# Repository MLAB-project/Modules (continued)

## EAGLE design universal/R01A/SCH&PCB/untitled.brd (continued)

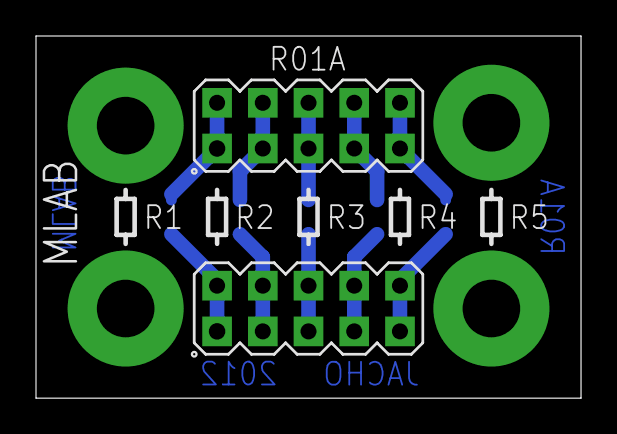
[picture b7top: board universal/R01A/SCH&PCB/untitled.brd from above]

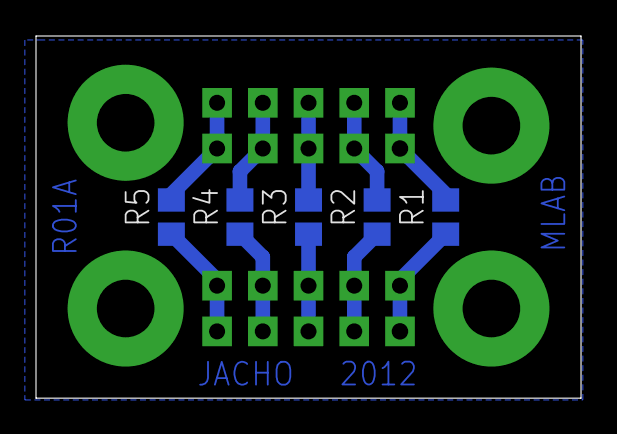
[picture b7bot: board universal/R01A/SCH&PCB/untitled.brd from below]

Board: 2 copper layers, 30.3 x 20.1 mm, 11 parts (5 on the bottom side), 11 nets.

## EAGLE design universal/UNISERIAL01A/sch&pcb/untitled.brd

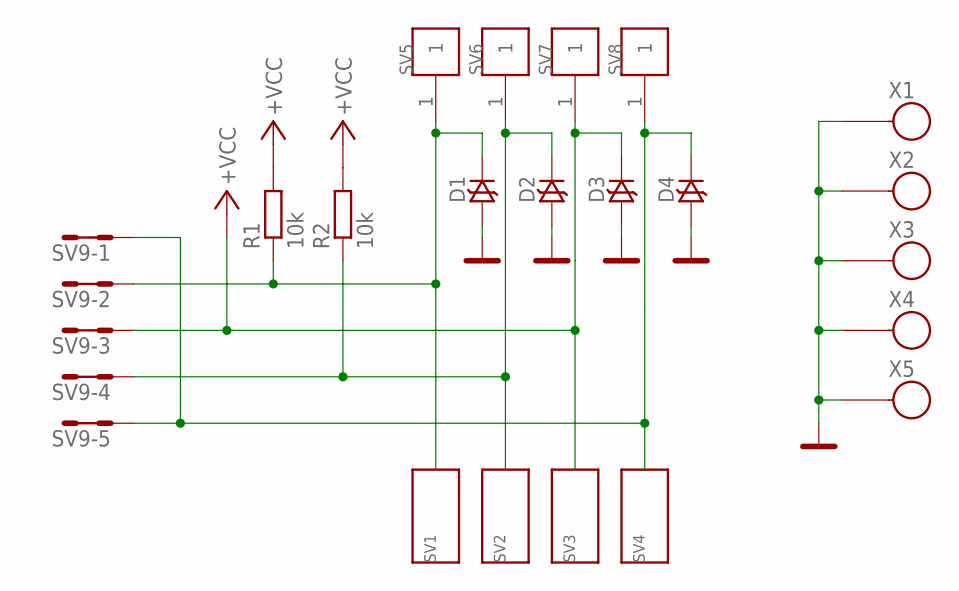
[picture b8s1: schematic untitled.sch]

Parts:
D1, D2, D3, D4: D-TRANSIL-SMA; SMA
R1, R2: 10k; 0805
SV1, SV2, SV3, SV4: WAGO256
SV5, SV6, SV7, SV8: SMD:MA01-01; SMD_MA01-1
SV9: MA05-2
X1, X2, X3, X4, X5: SROUB3M

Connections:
+VCC: D3.K, R1.2, R2.2, SV3.1, SV3.A1, SV7.1, SV9.5, SV9.6
GND: D1.A, D2.A, D3.A, D4.A, X1.P$1, X2.P$1, X3.P$1, X4.P$1, X5.P$1
unnamed: D1.K, R1.1, SV1.1, SV1.A1, SV5.1, SV9.3, SV9.4
unnamed: D2.K, R2.1, SV2.1, SV2.A1, SV6.1, SV9.7, SV9.8
unnamed: D4.K, SV4.1, SV4.A1, SV8.1, SV9.1, SV9.2, SV9.9, SV9.10

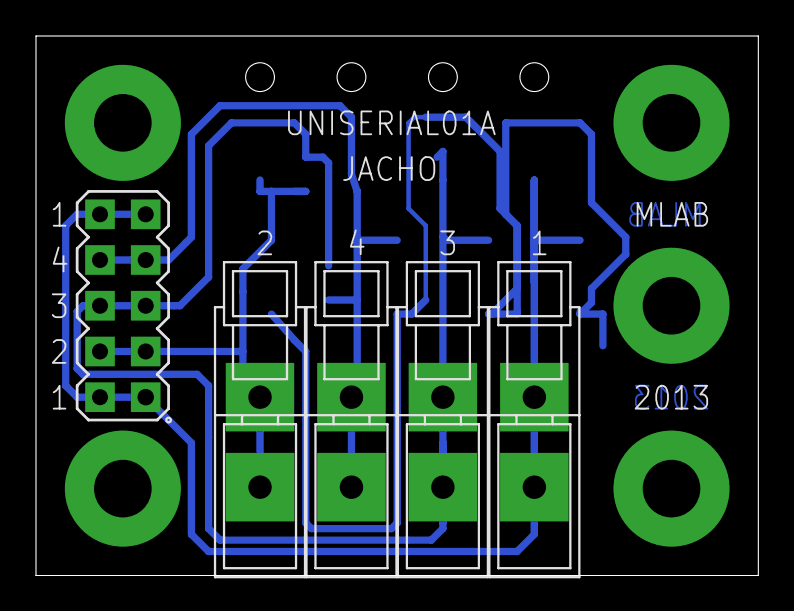
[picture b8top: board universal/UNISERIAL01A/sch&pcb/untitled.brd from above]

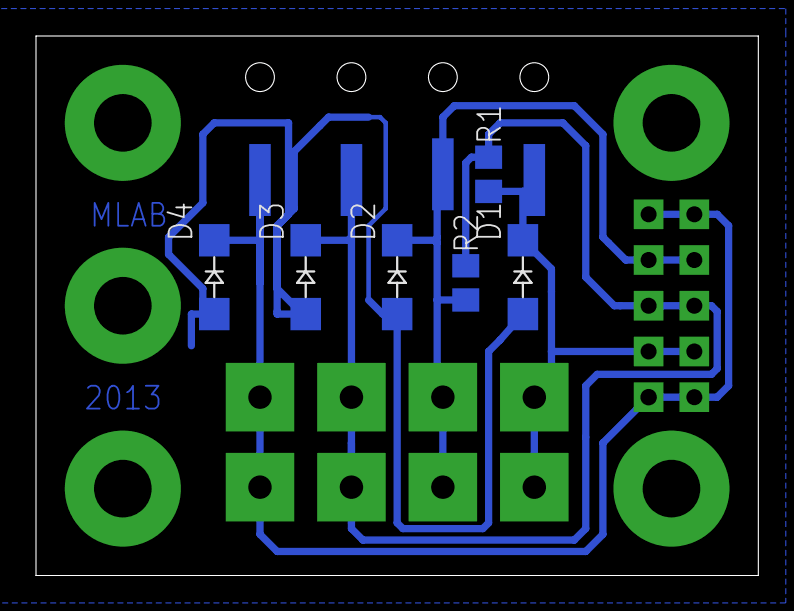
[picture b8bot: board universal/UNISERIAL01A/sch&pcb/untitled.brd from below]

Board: 2 copper layers, 40.1 x 30.0 mm, 20 parts (10 on the bottom side), 5 nets.

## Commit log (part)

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2022-02-16 [MLABweb] Documentation edits; TRIMQUAD01A
2022-02-16 [MLABweb] Documentation edits; LEDbar01A
2022-02-16 [MLABweb] Documentation edits; SDcard01A
2022-02-16 [MLABweb] Documentation edits; PIC16F87xTQ4401A
2022-02-16 [MLABweb] Documentation edits; PICICD01B
2022-02-16 [MLABweb] Documentation edits; Galileo
2022-02-16 [MLABweb] Documentation edits; ATmega8DIL01A
2022-02-16 [MLABweb] Documentation edits; AVRUSB01A
2022-02-16 [MLABweb] Documentation edits; ATmegaTQ10001A
2022-02-16 [MLABweb] Documentation edits; RFM02SMD01A
2022-02-16 [MLABweb] Documentation edits; BP01A
2022-02-16 [MLABweb] Documentation edits; PCRD01A
2022-02-16 [MLABweb] Documentation edits; S3AN01B
2022-02-16 [MLABweb] Documentation edits; LDD01A
2022-02-16 [MLABweb] Documentation edits; SMA2SATA01A
2022-02-16 [MLABweb] Documentation edits; HBRIDGE02A
2022-02-16 [MLABweb] Documentation edits; HBRIDGE01B
2022-02-16 [MLABweb] Documentation edits; MPC17511HB01A
2022-02-16 [MLABweb] Documentation edits; S3AN01A
2022-02-16 [MLABweb] Documentation edits; OZquad01A
2022-02-16 [MLABweb] Documentation edits; POWERDAC01A
2022-02-16 [MLABweb] Documentation edits; MBA81001A
2022-02-16 [MLABweb] Documentation edits; NFET2X01A
2022-02-16 [MLABweb] Documentation edits; PWMLED01A
2022-02-16 [MLABweb] Documentation edits; CLKGEN01A
2022-02-16 [MLABweb] Documentation edits; USB232R01A
2022-02-16 [MLABweb] Documentation edits; I2CHUB01B
2022-02-16 [MLABweb] Documentation edits; ETH01A
2022-02-16 [MLABweb] Documentation edits; SUPERCAP01A
2022-02-16 [MLABweb] Documentation edits; LION2CELL01C
2022-02-16 [MLABweb] Documentation edits; BATPOWER02A
2022-02-16 [MLABweb] Documentation edits; GPS02A
2022-02-17 [MLABweb] Documentation edits; CLKHUB01A
2022-02-17 Module moved to separate repository https://github.com/mlab-modules/ADCoctoSPI01
2022-02-17 Update submodule.
2022-02-18 Remove redundant files to submodules from the repository.
2022-03-08 TTLLVDS01A moved to separate submodule. https://github.com/mlab-modules/TTLLVDS01
2022-04-03 Add links to datasheets.
2022-04-03 Adding submodule STEPUPDC01A
2022-04-05 Adding USBI2C01A as submodule.
2022-04-05 Adding I2CHUB02 as submodule.
2022-08-14 Moving VCAI2C01 to separate repository. https://github.com/mlab-modules/VCAI2C01
2022-08-14 adding submodules of separate repositories.
2023-02-07 Removing ACOMP01A module. Will be designed from ground in the new repository.
2023-04-01 Removing ADC modules splitted to separate repositories.
2023-05-08 Removing ALBASE modules splitted to separate repositories.
2023-05-08 update split script
2023-05-08 Removing ALBASE1609 modules splitted to separate repositories.
2023-05-08 Removing ALBASE1608 modules splitted to separate repositories.
2023-05-08 Removing ALBASE1505 modules splitted to separate repositories.
2023-05-08 Removing ALBASE1241 modules splitted to separate repositories.
2023-05-08 Removing UNIPOWER02A modules splitted to separate repositories.
2023-05-09 Removing BATPOWER04C modules splitted to separate repositories.
2023-05-09 BATPOWER04 to submodule
2023-05-24 update submodule
2023-05-25 update submodle
2023-05-25 Removing CCP2019V01A modules splitted to separate repositories.
2023-05-25 Removing HCS01A modules splitted to separate repositories.
2023-05-25 Removing PIND01A modules splitted to separate repositories.
2023-05-25 Removing RGBC01A modules splitted to separate repositories.
2023-05-25 Removing RPS01A modules splitted to separate repositories.
2023-05-25 Removing SHT31V01A modules splitted to separate repositories.
2023-05-25 Removing THERMOPHILE01A modules splitted to separate repositories.
2023-05-25 Removing TTLPROBE02A modules splitted to separate repositories.
2023-05-25 Removing I2CDIFF01B modules splitted to separate repositories.
2023-05-25 Removing TTLPECL01A modules splitted to separate repositories.
2023-05-25 Removing HUM01A modules splitted to separate repositories.
2023-05-25 Removing IRFEE01A modules splitted to separate repositories.
2023-05-25 Removing ISL03A modules splitted to separate repositories.
2023-05-25 Removing IUC01A modules splitted to separate repositories.
2023-05-25 Removing LIGHTNING01A modules splitted to separate repositories.
2023-05-25 Removing MAG01A modules splitted to separate repositories.
2023-05-25 Removing Pulse_catch01A modules splitted to separate repositories.
2023-06-20 Removing ADCmonoPPI01A modules splitted to separate repositories.
2023-06-20 Removing ADCmonoSPI01B modules splitted to separate repositories.
2023-06-20 Removing ISPLSI1016A modules splitted to separate repositories.
2023-06-20 Removing S3AN01B modules splitted to separate repositories.
2023-06-20 Removing IRDA01A modules splitted to separate repositories.
2023-06-20 Removing TXIR01B modules splitted to separate repositories.
2023-06-20 Removing STM32F30xRx01A modules splitted to separate repositories.
2023-06-20 Removing ATmega801A modules splitted to separate repositories.
2023-06-20 Removing ATmega8DIL01A modules splitted to separate repositories.
2023-06-20 Removing ATmegaTQ3201A modules splitted to separate repositories.
2023-06-20 Removing ATmegaTQ6401A modules splitted to separate repositories.
2023-06-20 Removing ATprogISPUSB02A modules splitted to separate repositories.
2023-06-20 Removing ATtinySO801B modules splitted to separate repositories.
2023-06-20 Removing PICPROGUSB02A modules splitted to separate repositories.
2023-06-20 Removing PIC16F84SO1801A modules splitted to separate repositories.
2023-06-20 Removing PIC16F87xTQ4401B modules splitted to separate repositories.
2023-06-20 Removing PICPGR301A modules splitted to separate repositories.
2023-06-20 Removing PIC16F87xSO2801A modules splitted to separate repositories.
2023-06-20 Removing PIC16F87xDIL2801A modules splitted to separate repositories.
2023-06-20 Removing PIC18F2550v01A modules splitted to separate repositories.
2023-06-20 Removing PIC16F87xTQ4401A modules splitted to separate repositories.
2023-06-20 Removing RFdetect01A modules splitted to separate repositories.
2023-06-20 Removing BLE01A modules splitted to separate repositories.
2023-06-20 Removing RFM02SMD01A modules splitted to separate repositories.
2023-06-20 Removing TXsaw433MHz01A modules splitted to separate repositories.
2023-06-20 Removing GSM01A modules splitted to separate repositories.
2023-06-20 Removing RFM01SMD01A modules splitted to separate repositories.
2023-06-20 Removing BP01A modules splitted to separate repositories.
2023-06-20 Removing RFMIX01A modules splitted to separate repositories.
2023-06-20 Removing FORX01A modules splitted to separate repositories.
2023-06-20 Removing GSM01B modules splitted to separate repositories.
2023-06-20 Removing GP201A modules splitted to separate repositories.
2023-06-20 Removing ADCaudio01B modules splitted to separate repositories.
2023-06-20 Removing SYMTRANS01A modules splitted to separate repositories.
2023-06-20 Removing POWERDAC01A modules splitted to separate repositories.
2023-06-20 Removing AD1881A01A modules splitted to separate repositories.
2023-06-20 Removing CLKDIV01A modules splitted to separate repositories.
2023-06-20 Removing RTC03A modules splitted to separate repositories.
2023-06-20 Removing RTC01A modules splitted to separate repositories.
2023-06-20 Removing CLKGEN01B modules splitted to separate repositories.
2023-06-20 Removing CLKHUB02A modules splitted to separate repositories.
2023-06-20 Removing I2CHUB02B modules splitted to separate repositories.
2023-06-20 Removing SERVOHUB01A modules splitted to separate repositories.
2023-06-20 Removing I2CIO01A modules splitted to separate repositories.
2023-06-20 Removing I2CHUB01B modules splitted to separate repositories.
2023-06-20 Removing USBIO01A modules splitted to separate repositories.
2023-06-20 Removing TTLRS48501A modules splitted to separate repositories.
2023-06-20 Removing USBI2S01A modules splitted to separate repositories.
2023-06-20 Removing USB4xUART01A modules splitted to separate repositories.
2023-06-20 Removing ETH02A modules splitted to separate repositories.
2023-06-20 Removing TBPCIE01A modules splitted to separate repositories.
2023-06-20 Removing LED01A modules splitted to separate repositories.
2023-06-20 Removing DIP8SW01A modules splitted to separate repositories.
2023-06-20 Removing LCD2L4P01A modules splitted to separate repositories.
2023-06-20 Removing LEDbar01A modules splitted to separate repositories.
2023-06-20 Removing LED7SEG01A modules splitted to separate repositories.
2023-06-20 Removing nanoterm01A modules splitted to separate repositories.
2023-06-20 Removing SW01A modules splitted to separate repositories.
2023-06-20 Removing TOUCHBOARD01A modules splitted to separate repositories.
2023-06-20 Removing TRIM01A modules splitted to separate repositories.
2023-06-20 Removing AWSCREEN02A modules splitted to separate repositories.
2023-06-20 Removing BOXHOLDER01A modules splitted to separate repositories.
2023-06-20 Removing ISLHOLDER01A modules splitted to separate repositories.
2023-06-20 Removing RAINGUAGE01A modules splitted to separate repositories.
2023-06-20 Removing WINDGAUGE02A modules splitted to separate repositories.
2023-06-20 Removing EEPROM01A modules splitted to separate repositories.
2023-06-20 Removing SDcard01A modules splitted to separate repositories.
2023-06-20 Removing AXISCONTROL01A modules splitted to separate repositories.
2023-06-20 Removing DRV8835HB01B modules splitted to separate repositories.
2023-06-20 Removing HBRIDGE01B modules splitted to separate repositories.
2023-06-20 Removing HBRIDGE03A modules splitted to separate repositories.
2023-06-20 Removing HBSTEP01B modules splitted to separate repositories.
2023-06-20 Removing HB1FET01A modules splitted to separate repositories.
2023-06-20 Removing HT675101A modules splitted to separate repositories.
2023-06-20 Removing MPC17529HB01A modules splitted to separate repositories.
2023-06-20 Removing 3PHBRIDGE01A modules splitted to separate repositories.
2023-06-20 Removing OZDUAL02A modules splitted to separate repositories.
2023-06-20 Removing OZDUAL02B modules splitted to separate repositories.
2023-06-20 Removing OZDUAL03B modules splitted to separate repositories.
2023-06-20 Removing OZquad01A modules splitted to separate repositories.
2023-06-20 Removing ATXPOWER01A modules splitted to separate repositories.
2023-06-20 Removing BATPOWER02A modules splitted to separate repositories.
2023-06-20 Removing BATPOWER05A modules splitted to separate repositories.
2023-06-20 Removing DOWNCONV02A modules splitted to separate repositories.
2023-06-20 Removing CHPUMP01A modules splitted to separate repositories.
2023-06-20 Removing LM108601A modules splitted to separate repositories.
2023-06-20 Removing SOLAR01A modules splitted to separate repositories.
2023-06-20 Removing SUPERCAP01B modules splitted to separate repositories.
2023-06-20 Removing SYMPOWER02A modules splitted to separate repositories.
2023-06-20 Removing TPS63036V01A modules splitted to separate repositories.
2023-06-20 Removing UNIPOWER04A modules splitted to separate repositories.
2023-06-20 Removing UNIPOWER06A modules splitted to separate repositories.
2023-06-20 Removing UNIPOWER08A modules splitted to separate repositories.
2023-06-20 Removing COILSW01A modules splitted to separate repositories.
2023-06-20 Removing DIG4SW01A modules splitted to separate repositories.
2023-06-20 Removing NFET2X01A modules splitted to separate repositories.
2023-06-20 Removing NFET4X01B modules splitted to separate repositories.
2023-06-20 Removing PWMLED01B modules splitted to separate repositories.
2023-06-20 Removing REL1SW01A modules splitted to separate repositories.
2023-06-20 Removing TRIACSHARP02A modules splitted to separate repositories.
2023-06-20 Removing FMC2DIFF01A modules splitted to separate repositories.
2023-06-20 Removing RJ12V01A modules splitted to separate repositories.
2023-06-20 Removing RJ45V01A modules splitted to separate repositories.
2023-06-20 Removing UNIATMEGA8TQFP01A modules splitted to separate repositories.
2023-06-20 Removing UNISERIAL01A modules splitted to separate repositories.
